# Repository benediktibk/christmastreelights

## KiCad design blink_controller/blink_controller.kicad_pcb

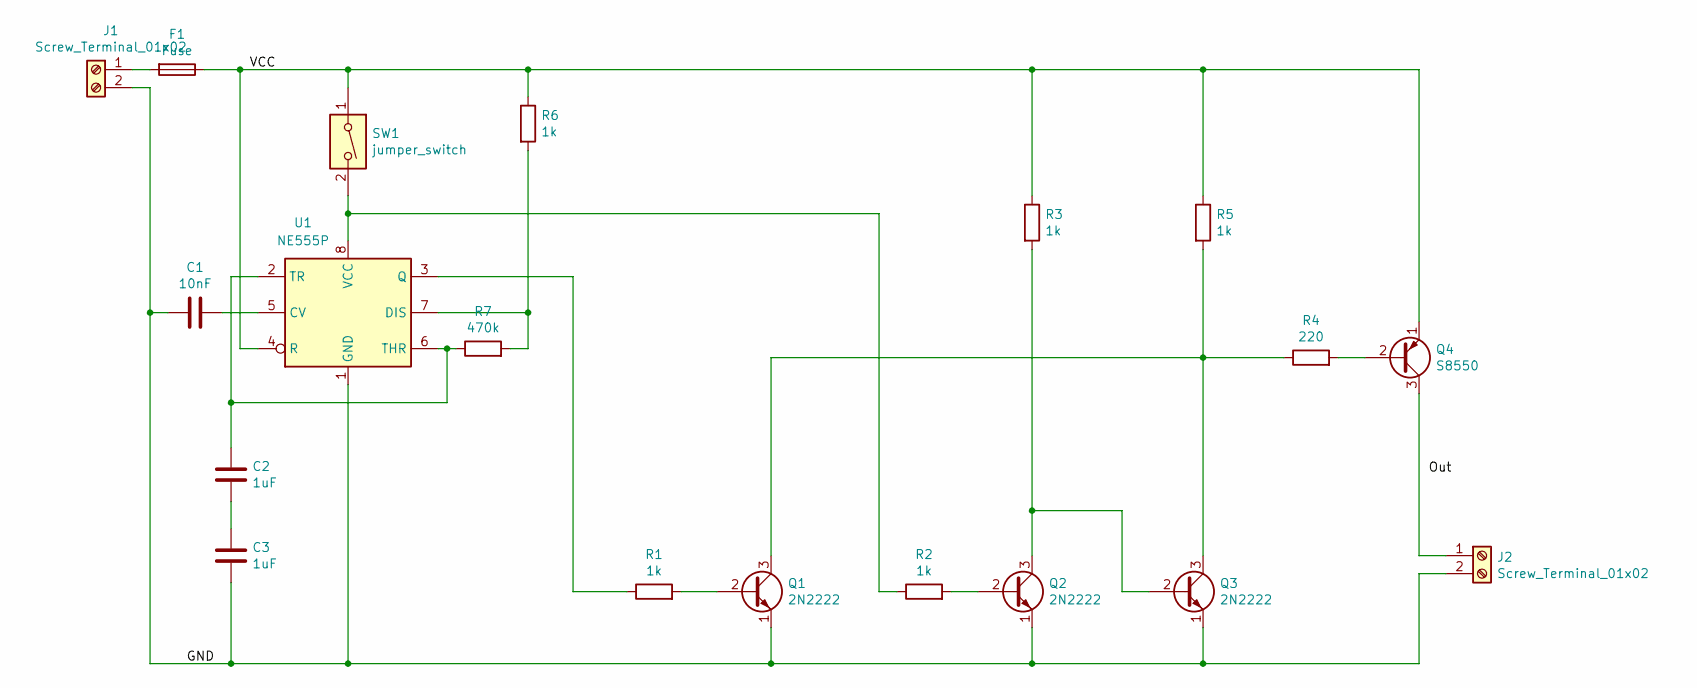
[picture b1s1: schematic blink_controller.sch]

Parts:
C1: 10nF; C_Disc_D5.1mm_W3.2mm_P5.00mm
C2, C3: 1uF; CP_Radial_D8.0mm_P3.80mm
F1: Fuse; Fuseholder_Cylinder-5x20mm_Schurter_0031_8201_Horizontal_Op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
J1, J2: Screw_Terminal_01x02; TerminalBlock_Altech_AK300-2_P5.00mm
Q1, Q2, Q3: 2N2222; 2N2222_Wide
Q4: S8550; S8550_wide
R1, R2, R3, R5, R6: 1k; R_Axial_DIN0207_L6.3mm_D2.5mm_P10.16mm_Horizontal
R4: 220; R_Axial_DIN0207_L6.3mm_D2.5mm_P10.16mm_Horizontal
R7: 470k; R_Axial_DIN0207_L6.3mm_D2.5mm_P10.16mm_Horizontal
SW1: jumper_switch
U1: NE555P; DIP-8_W7.62mm

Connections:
/GND: C1.2, C3.2, J1.2, J2.2, Q1.1 (E), Q2.1 (E), Q3.1 (E), U1.1 (GND)
/VCC: F1.1, Q4.1 (E), R3.1, R5.1, R6.1, SW1.1, U1.4 (R)
unnamed: C1.1, U1.5 (CV)
unnamed: C2.1, R7.1, U1.2 (TR), U1.6 (THR)
unnamed: C2.2, C3.1
unnamed: F1.2, J1.1
unnamed: J2.1, Q4.3 (C)
unnamed: Q1.2 (B), R1.2
unnamed: Q1.3 (C), Q3.3 (C), R4.1, R5.2
unnamed: Q2.2 (B), R2.2
unnamed: Q2.3 (C), Q3.2 (B), R3.2
unnamed: Q4.2 (B), R4.2
unnamed: R1.1, U1.3 (Q)
unnamed: R2.1, SW1.2, U1.8 (VCC)
unnamed: R6.2, R7.2, U1.7 (DIS)

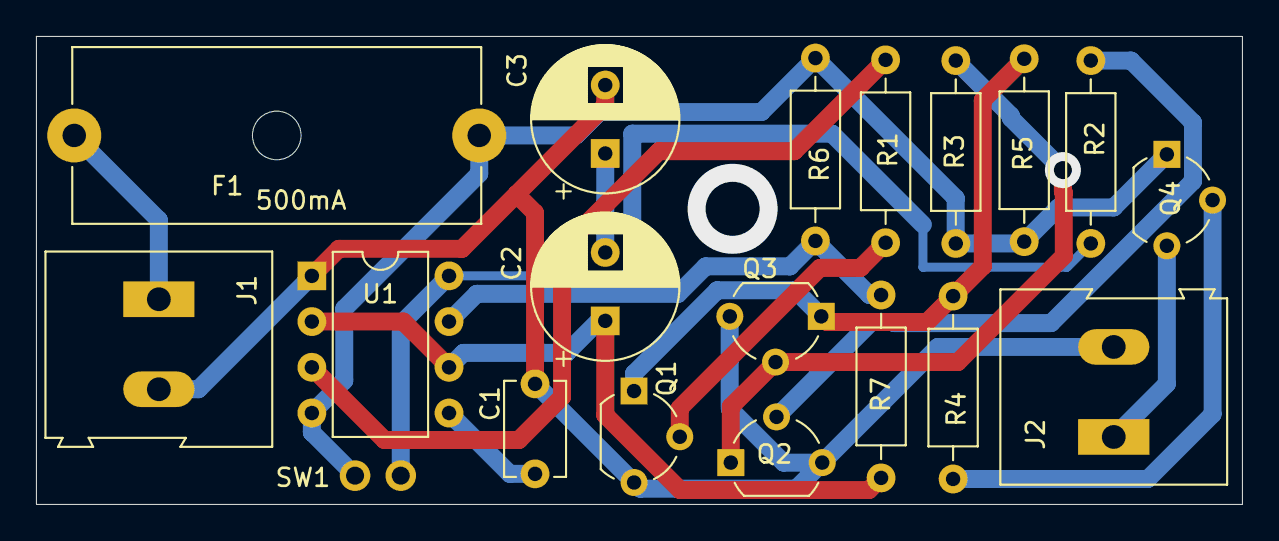
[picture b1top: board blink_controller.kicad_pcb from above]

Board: 2 copper layers, 67.0 x 26.0 mm, 19 parts (0 on the bottom side), 15 nets.

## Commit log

2020-11-27 Implement oscillator with Timer 555
2020-11-27 Finetune Circuit Design
2020-11-29 Make the blinking optional
2020-11-29 Reduce Power Loss
2020-12-08 Create schematic
2020-12-12 Finish schematic
2020-12-12 Create PCB
2020-12-12 Generate PCB plots
2020-12-12 Remove compressed plots
